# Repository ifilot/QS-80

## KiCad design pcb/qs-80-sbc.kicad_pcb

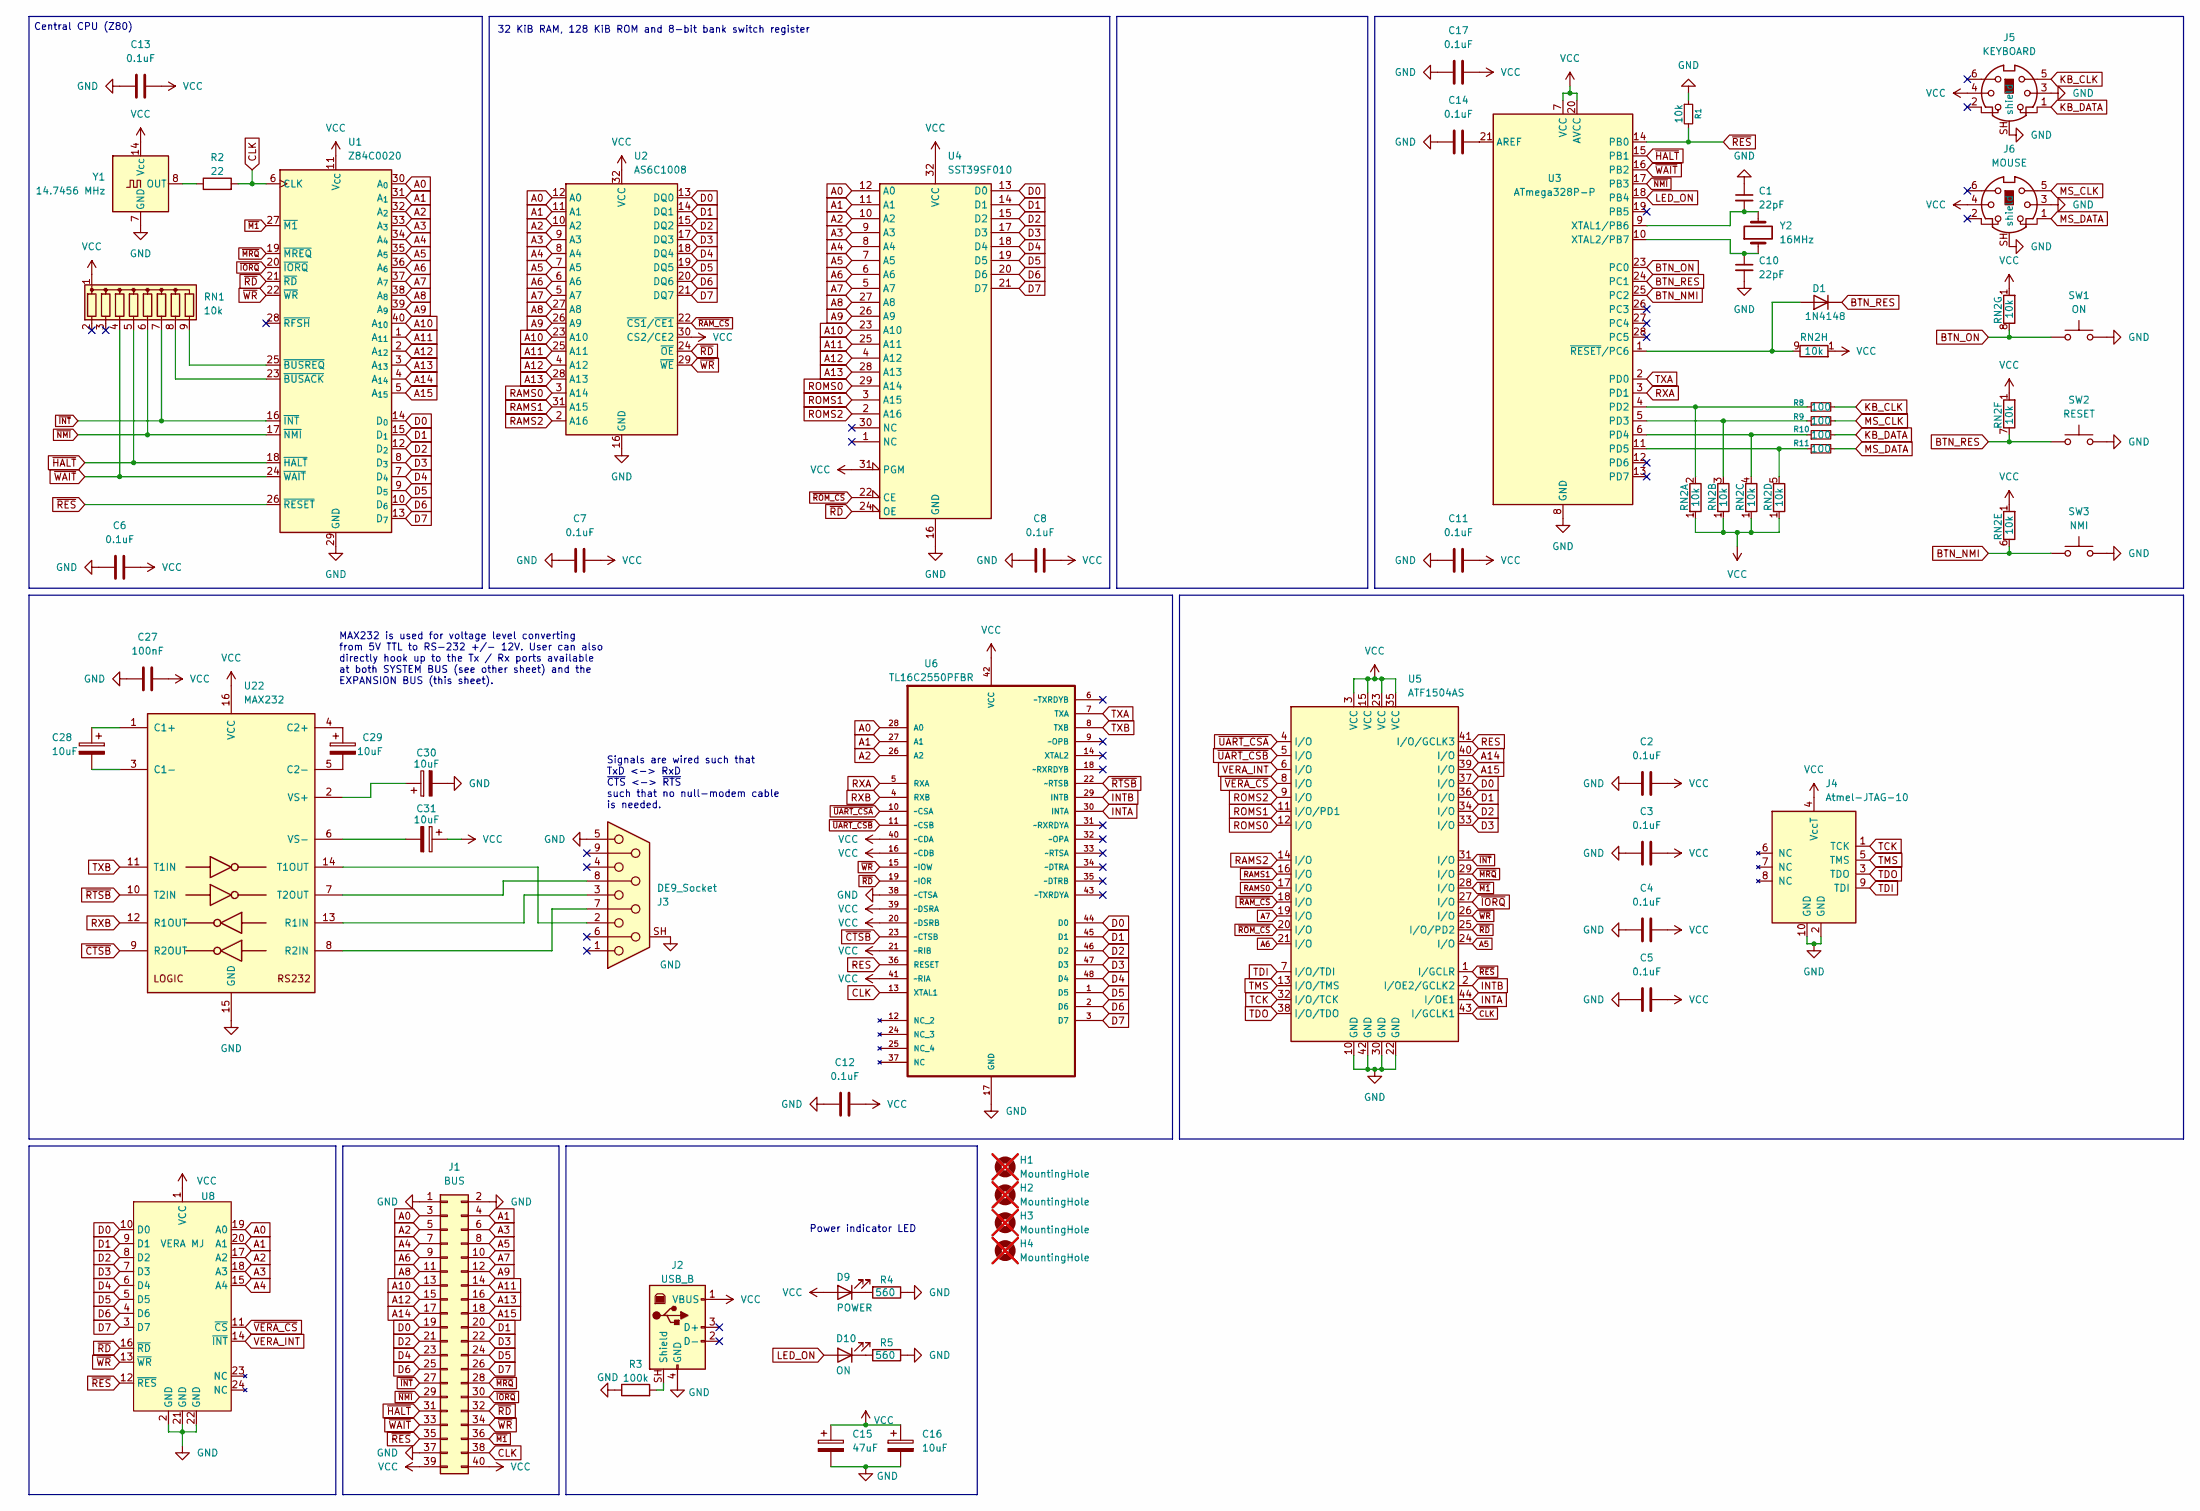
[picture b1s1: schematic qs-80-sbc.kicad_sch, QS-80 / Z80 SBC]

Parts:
C1, C10: 22pF; C_Disc_D5.0mm_W2.5mm_P5.00mm
C2, C3, C4, C5, C6, C7, C8, C11, C12, C13, C14, C17: 0.1uF; C_Disc_D5.0mm_W2.5mm_P5.00mm
C15: 47uF; CP_Radial_D6.3mm_P2.50mm
C16, C28, C29, C30, C31: 10uF; CP_Radial_D5.0mm_P2.50mm
C27: 100nF; C_Disc_D5.0mm_W2.5mm_P5.00mm
D1: 1N4148; D_DO-35_SOD27_P7.62mm_Horizontal
D9: POWER; LED_D5.0mm
D10: ON; LED_D5.0mm
H1, H2, H3, H4: MountingHole; MountingHole_3.2mm_M3_DIN965_Pad; not fitted
J1: BUS; PinHeader_2x20_P2.54mm_Vertical
J2: USB_B; USB_B_OST_USB-B1HSxx_Horizontal
J3: DE9_Socket; DSUB-9_Pins_Horizontal_P2.77x2.84mm_EdgePinOffset4.94mm_Hou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
J4: Atmel-JTAG-10; IDC-Header_2x05_P2.54mm_Vertical
J5: KEYBOARD; J_Mini-DIN-6
J6: MOUSE; J_Mini-DIN-6
R1: 10k; R_Axial_DIN0207_L6.3mm_D2.5mm_P7.62mm_Horizontal
R2: 22; R_Axial_DIN0207_L6.3mm_D2.5mm_P7.62mm_Horizontal
R3: 100k; R_Axial_DIN0207_L6.3mm_D2.5mm_P7.62mm_Horizontal
R4, R5: 560; R_Axial_DIN0207_L6.3mm_D2.5mm_P7.62mm_Horizontal
R8, R9, R10, R11: 100; R_Axial_DIN0207_L6.3mm_D2.5mm_P7.62mm_Horizontal
RN1, RN2: 10k; R_Array_SIP9
SW1: ON; SW_PUSH_6mm
SW2: RESET; SW_PUSH_6mm
SW3: NMI; SW_PUSH_6mm
U1: Z84C0020; DIP-40_W15.24mm_Socket
U2: AS6C1008; DIP-32_W15.24mm_Socket
U3: ATmega328P-P; DIP-28_W7.62mm_Socket
U4: SST39SF010; DIP-32_W15.24mm_Socket
U5: ATF1504AS; PLCC-44_THT-Socket
U6: TL16C2550PFBR; TQFP-48_7x7mm_P0.5mm; MPN TL16C2550PFBR
U8: VERA MJ; veraboard
U22: MAX232; DIP-16_W7.62mm_Socket
Y1: 14.7456 MHz; Oscillator_DIP-14
Y2: 16MHz; Crystal_HC49-U_Vertical

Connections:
A0: J1.3, U1.30 (A_{0}), U2.12 (A0), U4.12 (A0), U6.28 (A0), U8.19 (A0)
A1: J1.4, U1.31 (A_{1}), U2.11 (A1), U4.11 (A1), U6.27 (A1), U8.20 (A1)
A2: J1.5, U1.32 (A_{2}), U2.10 (A2), U4.10 (A2), U6.26 (A2), U8.17 (A2)
A3: J1.6, U1.33 (A_{3}), U2.9 (A3), U4.9 (A3), U8.18 (A3)
A4: J1.7, U1.34 (A_{4}), U2.8 (A4), U4.8 (A4), U8.15 (A4)
A5: J1.8, U1.35 (A_{5}), U2.7 (A5), U4.7 (A5), U5.24 (I/O)
A6: J1.9, U1.36 (A_{6}), U2.6 (A6), U4.6 (A6), U5.21 (I/O)
A7: J1.10, U1.37 (A_{7}), U2.5 (A7), U4.5 (A7), U5.19 (I/O)
A8: J1.11, U1.38 (A_{8}), U2.27 (A8), U4.27 (A8)
A9: J1.12, U1.39 (A_{9}), U2.26 (A9), U4.26 (A9)
A10: J1.13, U1.40 (A_{10}), U2.23 (A10), U4.23 (A10)
A11: J1.14, U1.1 (A_{11}), U2.25 (A11), U4.25 (A11)
A12: J1.15, U1.2 (A_{12}), U2.4 (A12), U4.4 (A12)
A13: J1.16, U1.3 (A_{13}), U2.28 (A13), U4.28 (A13)
A14: J1.17, U1.4 (A_{14}), U5.40 (I/O)
A15: J1.18, U1.5 (A_{15}), U5.39 (I/O)
BTN_NMI: RN2.6 (R5.2), SW3.1, U3.25 (PC2)
BTN_ON: RN2.8 (R7.2), SW1.1, U3.23 (PC0)
BTN_RES: D1.1 (K), RN2.7 (R6.2), SW2.1, U3.24 (PC1)
CLK: J1.38, R2.2, U1.6 (CLK), U5.43 (I/GCLK1), U6.13 (XTAL1)
D0: J1.19, U1.14 (D_{0}), U2.13 (DQ0), U4.13 (D0), U5.37 (I/O), U6.44 (D0), U8.10 (D0)
D1: J1.20, U1.15 (D_{1}), U2.14 (DQ1), U4.14 (D1), U5.36 (I/O), U6.45 (D1), U8.9 (D1)
D2: J1.21, U1.12 (D_{2}), U2.15 (DQ2), U4.15 (D2), U5.34 (I/O), U6.46 (D2), U8.8 (D2)
D3: J1.22, U1.8 (D_{3}), U2.17 (DQ3), U4.17 (D3), U5.33 (I/O), U6.47 (D3), U8.7 (D3)
D4: J1.23, U1.7 (D_{4}), U2.18 (DQ4), U4.18 (D4), U6.48 (D4), U8.6 (D4)
D5: J1.24, U1.9 (D_{5}), U2.19 (DQ5), U4.19 (D5), U6.1 (D5), U8.5 (D5)
D6: J1.25, U1.10 (D_{6}), U2.20 (DQ6), U4.20 (D6), U6.2 (D6), U8.4 (D6)
D7: J1.26, U1.13 (D_{7}), U2.21 (DQ7), U4.21 (D7), U6.3 (D7), U8.3 (D7)
GND: C1.1, C2.2, C3.2, C4.2, C5.2, C6.2, C7.2, C8.2, C10.2, C11.2, C12.2, C13.2, C14.2, C15.2, C16.2, C17.2, C27.2, C30.2, J1.1, J1.2, J1.37, J2.4 (GND), J3.5, J3.SH (shield), J4.2 (GND), J4.10 (GND), J5.3, J5.SH (shield_SH), J6.3, J6.SH (shield_SH), R1.1, R3.1, R4.1, R5.1, SW1.2, SW2.2, SW3.2, U1.29 (GND), U2.16 (GND), U3.8 (GND), U3.22 (GND), U4.16 (GND), U5.10 (GND), U5.22 (GND), U5.30 (GND), U5.42 (GND), U6.17 (GND), U6.38 (~CTSA), U8.2 (GND), U8.21 (GND), U8.22 (GND), U22.15 (GND), Y1.7 (GND)
INTA: U5.44 (I/OE1), U6.30 (INTA)
INTB: U5.2 (I/OE2/GCLK2), U6.29 (INTB)
KB_CLK: J5.5, R8.2
KB_DATA: J5.1, R10.2
LED_ON: D10.2 (A), U3.18 (PB4)
MS_CLK: J6.5, R9.2
MS_DATA: J6.1, R11.2
unnamed: D1.2 (A), RN2.9 (R8.2), U3.1 (~RESET/PC6)
unnamed: D9.1 (K), R4.2
unnamed: D10.1 (K), R5.2
unnamed: J2.SH (Shield), R3.2
unnamed: RN1.8 (R7), U1.23 (~BUSACK)
unnamed: RN1.9 (R8), U1.25 (~BUSREQ)
unnamed: R8.1, RN2.2 (R1.2), U3.4 (PD2)
unnamed: R9.1, RN2.3 (R2.2), U3.5 (PD3)
unnamed: R10.1, RN2.4 (R3.2), U3.6 (PD4)
unnamed: R11.1, RN2.5 (R4.2), U3.11 (PD5)
unnamed: C14.1, U3.21 (AREF)
unnamed: C1.2, U3.9 (XTAL1/PB6), Y2.2
unnamed: C10.1, U3.10 (XTAL2/PB7), Y2.1
unnamed: C28.1, U22.1 (C1+)
unnamed: C28.2, U22.3 (C1-)
unnamed: C29.1, U22.4 (C2+)
unnamed: C29.2, U22.5 (C2-)
unnamed: J3.3, U22.13 (R1IN)
unnamed: J3.7, U22.8 (R2IN)
unnamed: J3.2, U22.14 (T1OUT)
unnamed: J3.8, U22.7 (T2OUT)
unnamed: C30.1, U22.2 (VS+)
unnamed: C31.2, U22.6 (VS-)
unnamed: R2.1, Y1.8 (OUT)
RAMS0: U2.3 (A14), U5.17 (I/O)
RAMS1: U2.31 (A15), U5.16 (I/O)
RAMS2: U2.2 (A16), U5.14 (I/O)
RES: U5.41 (I/O/GCLK3), U6.36 (RESET)
ROMS0: U4.29 (A14), U5.12 (I/O)
ROMS1: U4.3 (A15), U5.11 (I/O/PD1)
ROMS2: U4.2 (A16), U5.9 (I/O)
RXA: U3.3 (PD1), U6.5 (RXA)
RXB: U6.4 (RXB), U22.12 (R1OUT)
TCK: J4.1 (TCK), U5.32 (I/O/TCK)
TDI: J4.9 (TDI), U5.7 (I/O/TDI)
TDO: J4.3 (TDO), U5.38 (I/O/TDO)
TMS: J4.5 (TMS), U5.13 (I/O/TMS)
TXA: U3.2 (PD0), U6.7 (TXA)
TXB: U6.8 (TXB), U22.11 (T1IN)
VCC: C2.1, C3.1, C4.1, C5.1, C6.1, C7.1, C8.1, C11.1, C12.1, C13.1, C15.1, C16.1, C17.1, C27.1, C31.1, D9.2 (A), J1.39, J1.40, J2.1 (VBUS), J4.4 (VccT), J5.4, J6.4, RN1.1 (common), RN2.1 (R1), U1.11 (V_{CC}), U2.30 (CS2/CE2), U2.32 (VCC), U3.7 (VCC), U3.20 (AVCC), U4.31 (PGM), U4.32 (VCC), U5.3 (VCC), U5.15 (VCC), U5.23 (VCC), U5.35 (VCC), U6.16 (~CDB), U6.20 (~DSRB), U6.21 (~RIB), U6.39 (~DSRA), U6.40 (~CDA), U6.41 (~RIA), U6.42 (VCC), U8.1 (VCC), U22.16 (VCC), Y1.14 (Vcc)
VERA_INT: U5.6 (I/O), U8.14 (~INT)
~CTSB: U6.23 (~CTSB), U22.9 (R2OUT)
~HALT: J1.31, RN1.5 (R4), U1.18 (~HALT), U3.15 (PB1)
~INT: J1.27, RN1.7 (R6), U1.16 (~INT), U5.31 (I/O)
~IORQ: J1.30, U1.20 (~IORQ), U5.27 (I/O)
~M1: J1.36, U1.27 (~M1), U5.28 (I/O)
~MRQ: J1.28, U1.19 (~MREQ), U5.29 (I/O)
~NMI: J1.29, RN1.6 (R5), U1.17 (~NMI), U3.17 (PB3)
~RAM_CS: U2.22 (~CS1/~CE1), U5.18 (I/O)
~RD: J1.32, U1.21 (~RD), U2.24 (~OE), U4.24 (OE), U5.25 (I/O/PD2), U6.19 (~IOR), U8.16 (~RD)
~RES: J1.35, R1.2, U1.26 (~RESET), U3.14 (PB0), U5.1 (I/GCLR), U8.12 (~RES)
~ROM_CS: U4.22 (CE), U5.20 (I/O)
~RTSB: U6.22 (~RTSB), U22.10 (T2IN)
~UART_CSA: U5.4 (I/O), U6.10 (~CSA)
~UART_CSB: U5.5 (I/O), U6.11 (~CSB)
~VERA_CS: U5.8 (I/O), U8.11 (~CS)
~WAIT: J1.33, RN1.4 (R3), U1.24 (~WAIT), U3.16 (PB2)
~WR: J1.34, U1.22 (~WR), U2.29 (~WE), U5.26 (I/O), U6.15 (~IOW), U8.13 (~WR)

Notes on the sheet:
32 KiB RAM, 128 KiB ROM and 8-bit bank switch register
Central CPU (Z80)
Signals are wired such that TxD <-> RxD ~{CTS} <-> ~{RTS} such that no null-modem cable is needed.
MAX232 is used for voltage level converting from 5V TTL to RS-232 +/- 12V. User can also directly hook up to the Tx / Rx ports available at both SYSTEM BUS (see other sheet) and the EXPANSION BUS (this sheet).
Power indicator LED

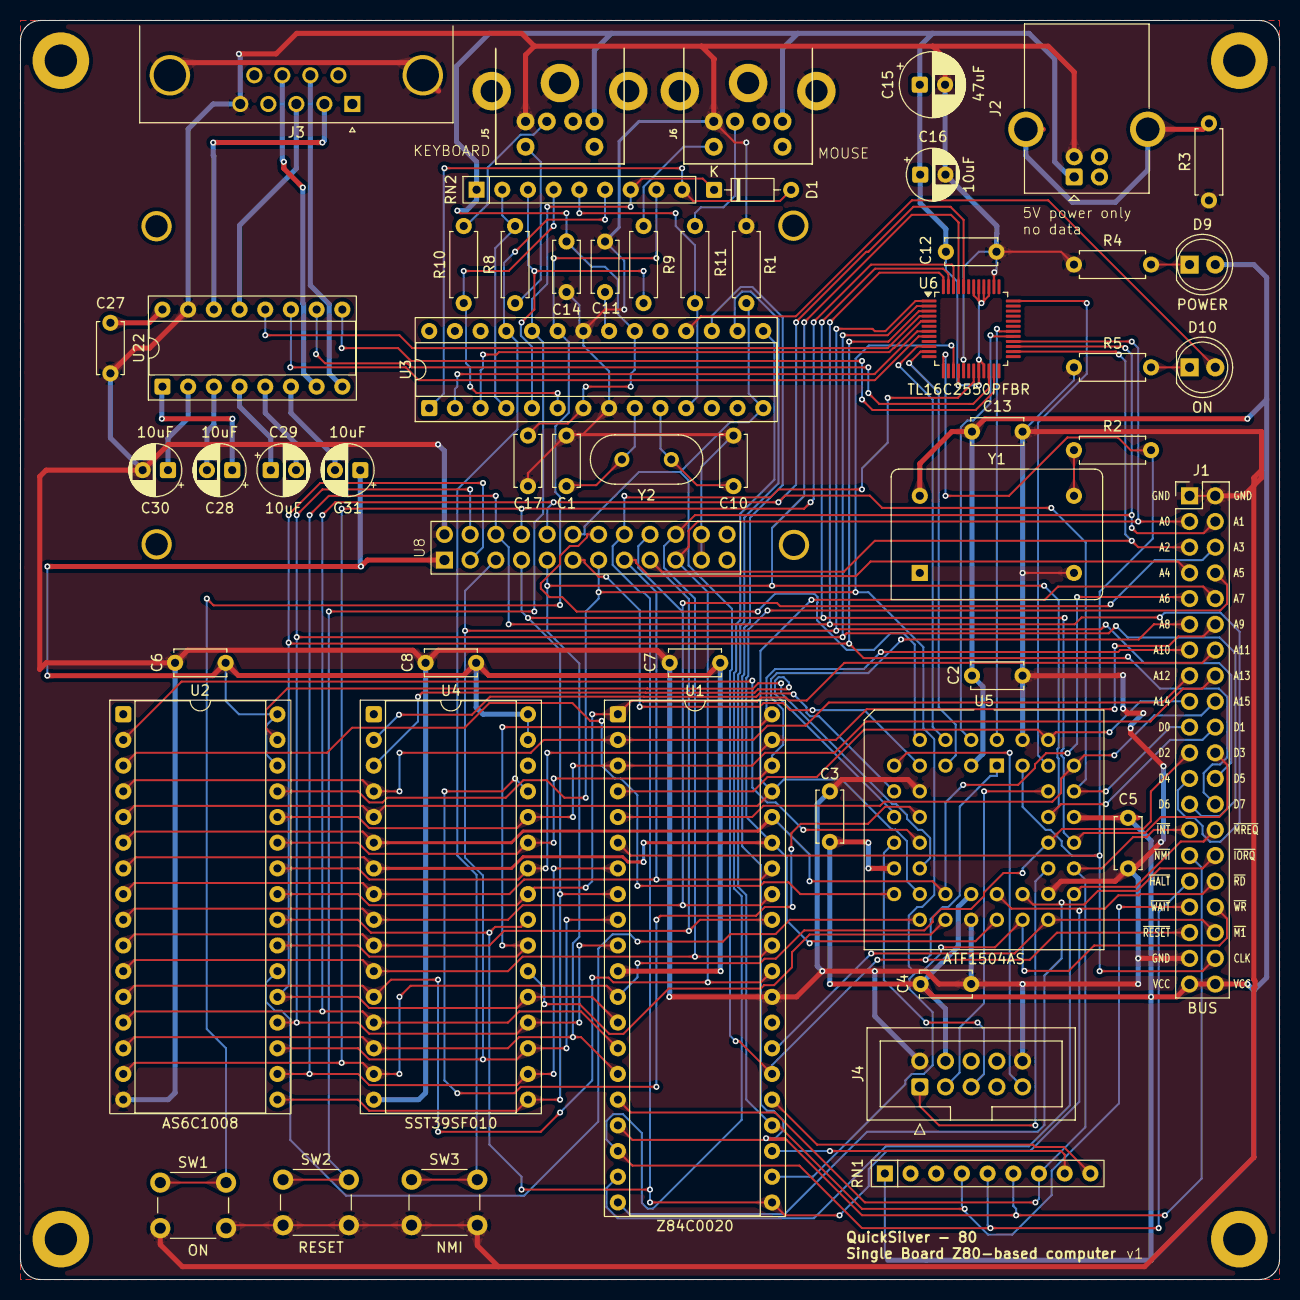
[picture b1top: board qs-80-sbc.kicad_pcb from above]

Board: 2 copper layers, 124.5 x 124.5 mm, 58 parts (0 on the bottom side), 94 nets.
